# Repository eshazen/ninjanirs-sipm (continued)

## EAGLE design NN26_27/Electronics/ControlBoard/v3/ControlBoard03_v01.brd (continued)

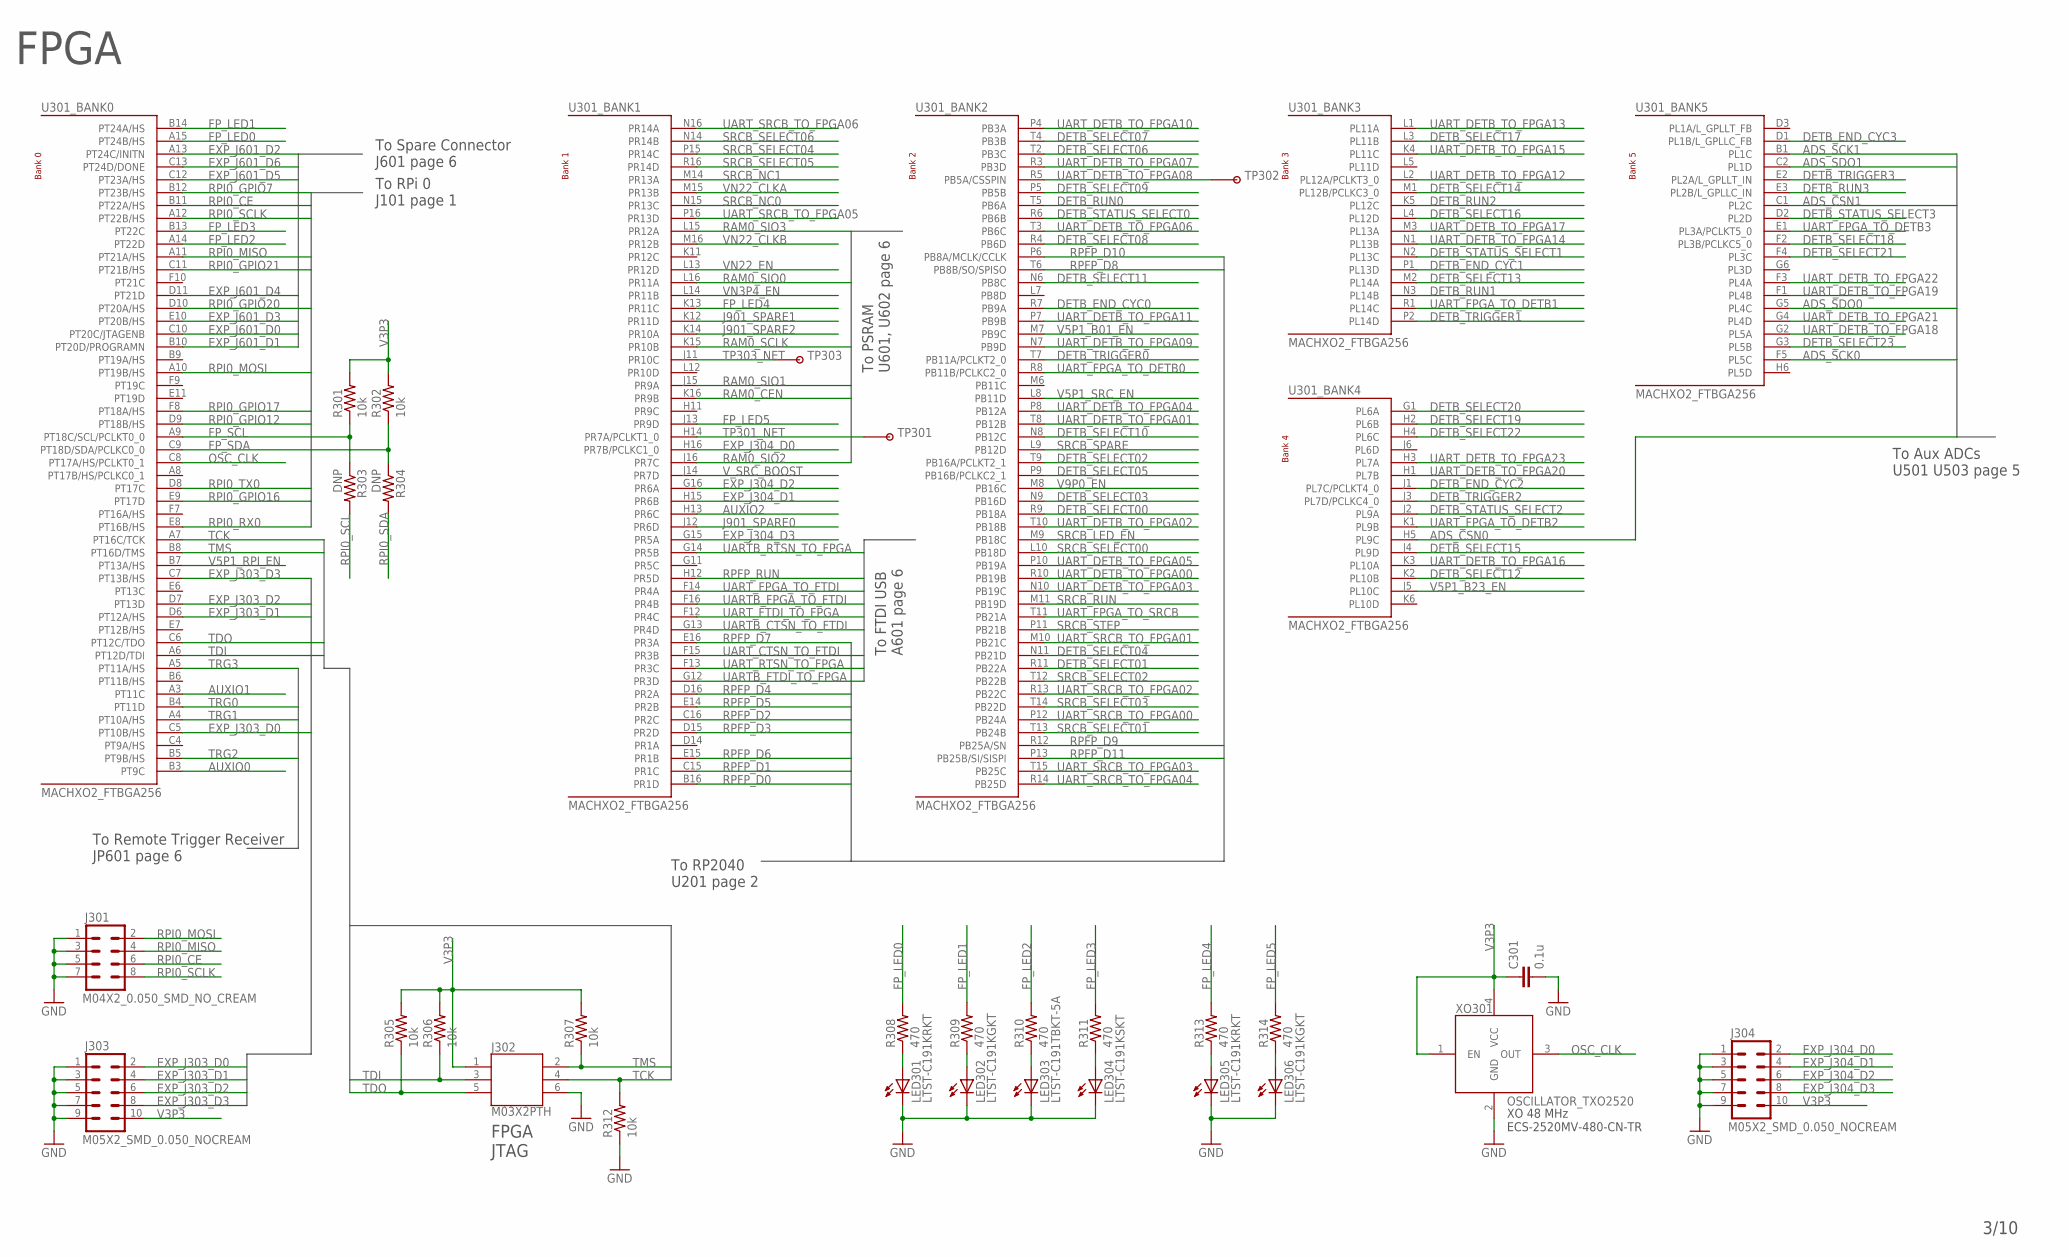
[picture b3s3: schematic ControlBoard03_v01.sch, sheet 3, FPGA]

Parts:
C301: 0.1u; 0402-CAP
J301: M04X2_0.050_SMD_NO_CREAM
J302: M03X2PTH; 2X3-NS
J303, J304: M05X2_SMD_0.050_NOCREAM; M05X2_0.050_SMD_NO_CREAM
LED301, LED305: LTST-C191KRKT; LED-0603
LED302, LED306: LTST-C191KGKT; LED-0603
LED303: LTST-C191TBKT-5A; LED-0603
LED304: LTST-C191KSKT; LED-0603
R301, R302, R305, R306, R307, R312: 10k; 0402-RES
R303, R304: DNP; 0402-RES
R308, R309, R310, R311, R313, R314: 470; 0402-RES
TP301, TP303: TESTPOINT_ROUND; TESTPAD_ROUND
TP302: TESTPOINTPADSMALL; TESTPAD_SMALL
U301: MACHXO2_FTBGA256; LBGA-256
XO301: OSCILLATOR_TXO2520; TXO2520

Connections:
ADS_CSN0: U301.H5 (PL9C); also elsewhere on the board
ADS_CSN1: U301.C1 (PL2C); also elsewhere on the board
ADS_SCK0: U301.F5 (PL5C); also elsewhere on the board
ADS_SCK1: U301.B1 (PL1C); also elsewhere on the board
ADS_SDO0: U301.G5 (PL4C); also elsewhere on the board
ADS_SDO1: U301.C2 (PL1D); also elsewhere on the board
AUXIO0: U301.B3 (PT9C); also elsewhere on the board
AUXIO1: U301.A3 (PT11C); also elsewhere on the board
AUXIO2: U301.H13 (PR6C); also elsewhere on the board
DETB_END_CYC0: U301.R7 (PB9A); also elsewhere on the board
DETB_END_CYC1: U301.P1 (PL13D); also elsewhere on the board
DETB_END_CYC2: U301.J1 (PL7C/PCLKT4_0); also elsewhere on the board
DETB_END_CYC3: U301.D1 (PL1B/L_GPLLC_FB); also elsewhere on the board
DETB_RUN0: U301.T5 (PB6A); also elsewhere on the board
DETB_RUN1: U301.N3 (PL14B); also elsewhere on the board
DETB_RUN2: U301.K5 (PL12C); also elsewhere on the board
DETB_RUN3: U301.E3 (PL2B/L_GPLLC_IN); also elsewhere on the board
DETB_SELECT00: U301.R9 (PB18A); also elsewhere on the board
DETB_SELECT01: U301.R11 (PB22A); also elsewhere on the board
DETB_SELECT02: U301.T9 (PB16A/PCLKT2_1); also elsewhere on the board
DETB_SELECT03: U301.N9 (PB16D); also elsewhere on the board
DETB_SELECT04: U301.N11 (PB21D); also elsewhere on the board
DETB_SELECT05: U301.P9 (PB16B/PCLKC2_1); also elsewhere on the board
DETB_SELECT06: U301.T2 (PB3C); also elsewhere on the board
DETB_SELECT07: U301.T4 (PB3B); also elsewhere on the board
DETB_SELECT08: U301.R4 (PB6D); also elsewhere on the board
DETB_SELECT09: U301.P5 (PB5B); also elsewhere on the board
DETB_SELECT10: U301.N8 (PB12C); also elsewhere on the board
DETB_SELECT11: U301.N6 (PB8C); also elsewhere on the board
DETB_SELECT12: U301.K2 (PL10B); also elsewhere on the board
DETB_SELECT13: U301.M2 (PL14A); also elsewhere on the board
DETB_SELECT14: U301.M1 (PL12B/PCLKC3_0); also elsewhere on the board
DETB_SELECT15: U301.J4 (PL9D); also elsewhere on the board
DETB_SELECT16: U301.L4 (PL12D); also elsewhere on the board
DETB_SELECT17: U301.L3 (PL11B); also elsewhere on the board
DETB_SELECT18: U301.F2 (PL3B/PCLKC5_0); also elsewhere on the board
DETB_SELECT19: U301.H2 (PL6B); also elsewhere on the board
DETB_SELECT20: U301.G1 (PL6A); also elsewhere on the board
DETB_SELECT21: U301.F4 (PL3C); also elsewhere on the board
DETB_SELECT22: U301.H4 (PL6C); also elsewhere on the board
DETB_SELECT23: U301.G3 (PL5B); also elsewhere on the board
DETB_STATUS_SELECT0: U301.R6 (PB6B); also elsewhere on the board
DETB_STATUS_SELECT1: U301.N2 (PL13C); also elsewhere on the board
DETB_STATUS_SELECT2: U301.J2 (PL9A); also elsewhere on the board
DETB_STATUS_SELECT3: U301.D2 (PL2D); also elsewhere on the board
DETB_TRIGGER0: U301.T7 (PB11A/PCLKT2_0); also elsewhere on the board
DETB_TRIGGER1: U301.P2 (PL14D); also elsewhere on the board
DETB_TRIGGER2: U301.J3 (PL7D/PCLKC4_0); also elsewhere on the board
DETB_TRIGGER3: U301.E2 (PL2A/L_GPLLT_IN); also elsewhere on the board
EXP_J303_D0: J303.2, U301.C5 (PT10B/HS)
EXP_J303_D1: J303.4, U301.D6 (PT12A/HS)
EXP_J303_D2: J303.6, U301.D7 (PT13D)
EXP_J303_D3: J303.8, U301.C7 (PT13B/HS)
EXP_J304_D0: J304.2, U301.H16 (PR7B/PCLKC1_0)
EXP_J304_D1: J304.4, U301.H15 (PR6B)
EXP_J304_D2: J304.6, U301.G16 (PR6A)
EXP_J304_D3: J304.8, U301.G15 (PR5A)
EXP_J601_D0: U301.C10 (PT20C/JTAGENB); also elsewhere on the board
EXP_J601_D1: U301.B10 (PT20D/PROGRAMN); also elsewhere on the board
EXP_J601_D2: U301.A13 (PT24C/INITN); also elsewhere on the board
EXP_J601_D3: U301.E10 (PT20B/HS); also elsewhere on the board
EXP_J601_D4: U301.D11 (PT21D); also elsewhere on the board
EXP_J601_D5: U301.C12 (PT23A/HS); also elsewhere on the board
EXP_J601_D6: U301.C13 (PT24D/DONE); also elsewhere on the board
FP_LED0: R308.2, U301.A15 (PT24B/HS)
FP_LED1: R309.2, U301.B14 (PT24A/HS)
FP_LED2: R310.2, U301.A14 (PT22D)
FP_LED3: R311.2, U301.B13 (PT22C)
FP_LED4: R313.2, U301.K13 (PR11C)
FP_LED5: R314.2, U301.J13 (PR9D)
FP_SCL: R301.1, R303.1, U301.A9 (PT18C/SCL/PCLKT0_0)
FP_SDA: R302.1, R304.1, U301.C9 (PT18D/SDA/PCLKC0_0)
GND: C301.2, J301.1, J301.3, J301.5, J301.7, J302.6, J303.1, J303.3, J303.5, J303.7, J303.9, J304.1, J304.3, J304.5, J304.7, J304.9, LED301.C, LED302.C, LED303.C, LED304.C, LED305.C, LED306.C, R312.1, XO301.2 (GND); also elsewhere on the board
J901_SPARE0: U301.J12 (PR6D); also elsewhere on the board
J901_SPARE1: U301.K12 (PR11D); also elsewhere on the board
J901_SPARE2: U301.K14 (PR10A); also elsewhere on the board
unnamed: LED301.A, R308.1
unnamed: LED302.A, R309.1
unnamed: LED303.A, R310.1
unnamed: LED304.A, R311.1
unnamed: LED305.A, R313.1
unnamed: LED306.A, R314.1
OSC_CLK: U301.C8 (PT17A/HS/PCLKT0_1), XO301.3 (OUT)
RAM0_CEN: U301.K16 (PR9B); also elsewhere on the board
RAM0_SCLK: U301.K15 (PR10B); also elsewhere on the board
RAM0_SIO0: U301.L16 (PR11A); also elsewhere on the board
RAM0_SIO1: U301.J15 (PR9A); also elsewhere on the board
RAM0_SIO2: U301.J16 (PR7C); also elsewhere on the board
RAM0_SIO3: U301.L15 (PR12A); also elsewhere on the board
RPFP_D0: U301.B16 (PR1D); also elsewhere on the board
RPFP_D1: U301.C15 (PR1C); also elsewhere on the board
RPFP_D2: U301.C16 (PR2C); also elsewhere on the board
RPFP_D3: U301.D15 (PR2D); also elsewhere on the board
RPFP_D4: U301.D16 (PR2A); also elsewhere on the board
RPFP_D5: U301.E14 (PR2B); also elsewhere on the board
RPFP_D6: U301.E15 (PR1B); also elsewhere on the board
RPFP_D7: U301.E16 (PR3A); also elsewhere on the board
RPFP_D8: U301.T6 (PB8B/SO/SPISO); also elsewhere on the board
RPFP_D9: U301.R12 (PB25A/SN); also elsewhere on the board
RPFP_D10: U301.P6 (PB8A/MCLK/CCLK); also elsewhere on the board
RPFP_D11: U301.P13 (PB25B/SI/SISPI); also elsewhere on the board
RPFP_RUN: U301.H12 (PR5D); also elsewhere on the board
RPI0_CE: J301.6, U301.B11 (PT22A/HS); also elsewhere on the board
RPI0_GPIO7: U301.B12 (PT23B/HS); also elsewhere on the board
RPI0_GPIO12: U301.D9 (PT18B/HS); also elsewhere on the board
RPI0_GPIO16: U301.E9 (PT17D); also elsewhere on the board
RPI0_GPIO17: U301.F8 (PT18A/HS); also elsewhere on the board
RPI0_GPIO20: U301.D10 (PT20A/HS); also elsewhere on the board
RPI0_GPIO21: U301.C11 (PT21B/HS); also elsewhere on the board
RPI0_MISO: J301.4, U301.A11 (PT21A/HS); also elsewhere on the board
RPI0_MOSI: J301.2, U301.A10 (PT19B/HS); also elsewhere on the board
RPI0_RX0: U301.E8 (PT16B/HS); also elsewhere on the board
RPI0_SCL: R303.2; also elsewhere on the board
RPI0_SCLK: J301.8, U301.A12 (PT22B/HS); also elsewhere on the board
RPI0_SDA: R304.2; also elsewhere on the board
RPI0_TX0: U301.D8 (PT17C); also elsewhere on the board
SRCB_LED_EN: U301.M9 (PB18C); also elsewhere on the board
SRCB_NC0: U301.N15 (PR13C); also elsewhere on the board
SRCB_NC1: U301.M14 (PR13A); also elsewhere on the board
SRCB_RUN: U301.M11 (PB19D); also elsewhere on the board
SRCB_SELECT00: U301.L10 (PB18D); also elsewhere on the board
SRCB_SELECT01: U301.T13 (PB24B); also elsewhere on the board
SRCB_SELECT02: U301.T12 (PB22B); also elsewhere on the board
SRCB_SELECT03: U301.T14 (PB22D); also elsewhere on the board
SRCB_SELECT04: U301.P15 (PR14C); also elsewhere on the board
SRCB_SELECT05: U301.R16 (PR14D); also elsewhere on the board
SRCB_SELECT06: U301.N14 (PR14B); also elsewhere on the board
SRCB_SPARE: U301.L9 (PB12D); also elsewhere on the board
SRCB_STEP: U301.P11 (PB21B); also elsewhere on the board
TCK: J302.4, R312.2, U301.A7 (PT16C/TCK)
TDI: J302.3, R306.1, U301.A6 (PT12D/TDI)
TDO: J302.5, R305.1, U301.C6 (PT12C/TDO)
TMS: J302.2, R307.1, U301.B8 (PT16D/TMS)
TP301_NET: TP301.P$1, U301.H14 (PR7A/PCLKT1_0)
TP303_NET: TP303.P$1, U301.J11 (PR10C)
TRG0: U301.B4 (PT11D); also elsewhere on the board
TRG1: U301.A4 (PT10A/HS); also elsewhere on the board
TRG2: U301.B5 (PT9B/HS); also elsewhere on the board
TRG3: U301.A5 (PT11A/HS); also elsewhere on the board
UARTB_CTSN_TO_FTDI: U301.G13 (PR4D); also elsewhere on the board
UARTB_FPGA_TO_FTDI: U301.F16 (PR4B); also elsewhere on the board
UARTB_FTDI_TO_FPGA: U301.G12 (PR3D); also elsewhere on the board
UARTB_RTSN_TO_FPGA: U301.G14 (PR5B); also elsewhere on the board
UART_CTSN_TO_FTDI: U301.F15 (PR3B); also elsewhere on the board
UART_DETB_TO_FPGA00: U301.R10 (PB19B); also elsewhere on the board
UART_DETB_TO_FPGA01: U301.T8 (PB12B); also elsewhere on the board
UART_DETB_TO_FPGA02: U301.T10 (PB18B); also elsewhere on the board
UART_DETB_TO_FPGA03: U301.N10 (PB19C); also elsewhere on the board
UART_DETB_TO_FPGA04: U301.P8 (PB12A); also elsewhere on the board
UART_DETB_TO_FPGA05: U301.P10 (PB19A); also elsewhere on the board
UART_DETB_TO_FPGA06: U301.T3 (PB6C); also elsewhere on the board
UART_DETB_TO_FPGA07: U301.R3 (PB3D); also elsewhere on the board
UART_DETB_TO_FPGA08: TP302.P$1, U301.R5 (PB5A/CSSPIN); also elsewhere on the board
UART_DETB_TO_FPGA09: U301.N7 (PB9D); also elsewhere on the board
UART_DETB_TO_FPGA10: U301.P4 (PB3A); also elsewhere on the board
UART_DETB_TO_FPGA11: U301.P7 (PB9B); also elsewhere on the board
UART_DETB_TO_FPGA12: U301.L2 (PL12A/PCLKT3_0); also elsewhere on the board
UART_DETB_TO_FPGA13: U301.L1 (PL11A); also elsewhere on the board
UART_DETB_TO_FPGA14: U301.N1 (PL13B); also elsewhere on the board
UART_DETB_TO_FPGA15: U301.K4 (PL11C); also elsewhere on the board
UART_DETB_TO_FPGA16: U301.K3 (PL10A); also elsewhere on the board
UART_DETB_TO_FPGA17: U301.M3 (PL13A); also elsewhere on the board
UART_DETB_TO_FPGA18: U301.G2 (PL5A); also elsewhere on the board
UART_DETB_TO_FPGA19: U301.F1 (PL4B); also elsewhere on the board
UART_DETB_TO_FPGA20: U301.H1 (PL7B); also elsewhere on the board
UART_DETB_TO_FPGA21: U301.G4 (PL4D); also elsewhere on the board
UART_DETB_TO_FPGA22: U301.F3 (PL4A); also elsewhere on the board
UART_DETB_TO_FPGA23: U301.H3 (PL7A); also elsewhere on the board
UART_FPGA_TO_DETB0: U301.R8 (PB11B/PCLKC2_0); also elsewhere on the board
UART_FPGA_TO_DETB1: U301.R1 (PL14C); also elsewhere on the board
UART_FPGA_TO_DETB2: U301.K1 (PL9B); also elsewhere on the board
UART_FPGA_TO_DETB3: U301.E1 (PL3A/PCLKT5_0); also elsewhere on the board
UART_FPGA_TO_FTDI: U301.F14 (PR4A); also elsewhere on the board
UART_FPGA_TO_SRCB: U301.T11 (PB21A); also elsewhere on the board
UART_FTDI_TO_FPGA: U301.F12 (PR4C); also elsewhere on the board
UART_RTSN_TO_FPGA: U301.F13 (PR3C); also elsewhere on the board
UART_SRCB_TO_FPGA00: U301.P12 (PB24A); also elsewhere on the board
UART_SRCB_TO_FPGA01: U301.M10 (PB21C); also elsewhere on the board
UART_SRCB_TO_FPGA02: U301.R13 (PB22C); also elsewhere on the board
UART_SRCB_TO_FPGA03: U301.T15 (PB25C); also elsewhere on the board
UART_SRCB_TO_FPGA04: U301.R14 (PB25D); also elsewhere on the board
UART_SRCB_TO_FPGA05: U301.P16 (PR13D); also elsewhere on the board
UART_SRCB_TO_FPGA06: U301.N16 (PR14A); also elsewhere on the board
V3P3: C301.1, J302.1, J303.10, J304.10, R301.2, R302.2, R305.2, R306.2, R307.2, XO301.1 (EN), XO301.4 (VCC); also elsewhere on the board
V5P1_B01_EN: U301.M7 (PB9C); also elsewhere on the board
V5P1_B23_EN: U301.J5 (PL10C); also elsewhere on the board
V5P1_RPI_EN: U301.B7 (PT13A/HS); also elsewhere on the board
V5P1_SRC_EN: U301.L8 (PB11D); also elsewhere on the board
V9P0_EN: U301.M8 (PB16C); also elsewhere on the board
VN3P4_EN: U301.L14 (PR11B); also elsewhere on the board
VN22_CLKA: U301.M15 (PR13B); also elsewhere on the board
VN22_CLKB: U301.M16 (PR12B); also elsewhere on the board
VN22_EN: U301.L13 (PR12D); also elsewhere on the board
V_SRC_BOOST: U301.J14 (PR7D); also elsewhere on the board

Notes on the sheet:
XO 48 MHz ECS-2520MV-480-CN-TR
FPGA
FPGA JTAG
To RPi 0 J101 page 1
To RP2040 U201 page 2
To FTDI USB A601 page 6
To Spare Connector J601 page 6
To Remote Trigger Receiver JP601 page 6
To Aux ADCs U501 U503 page 5
To PSRAM U601, U602 page 6

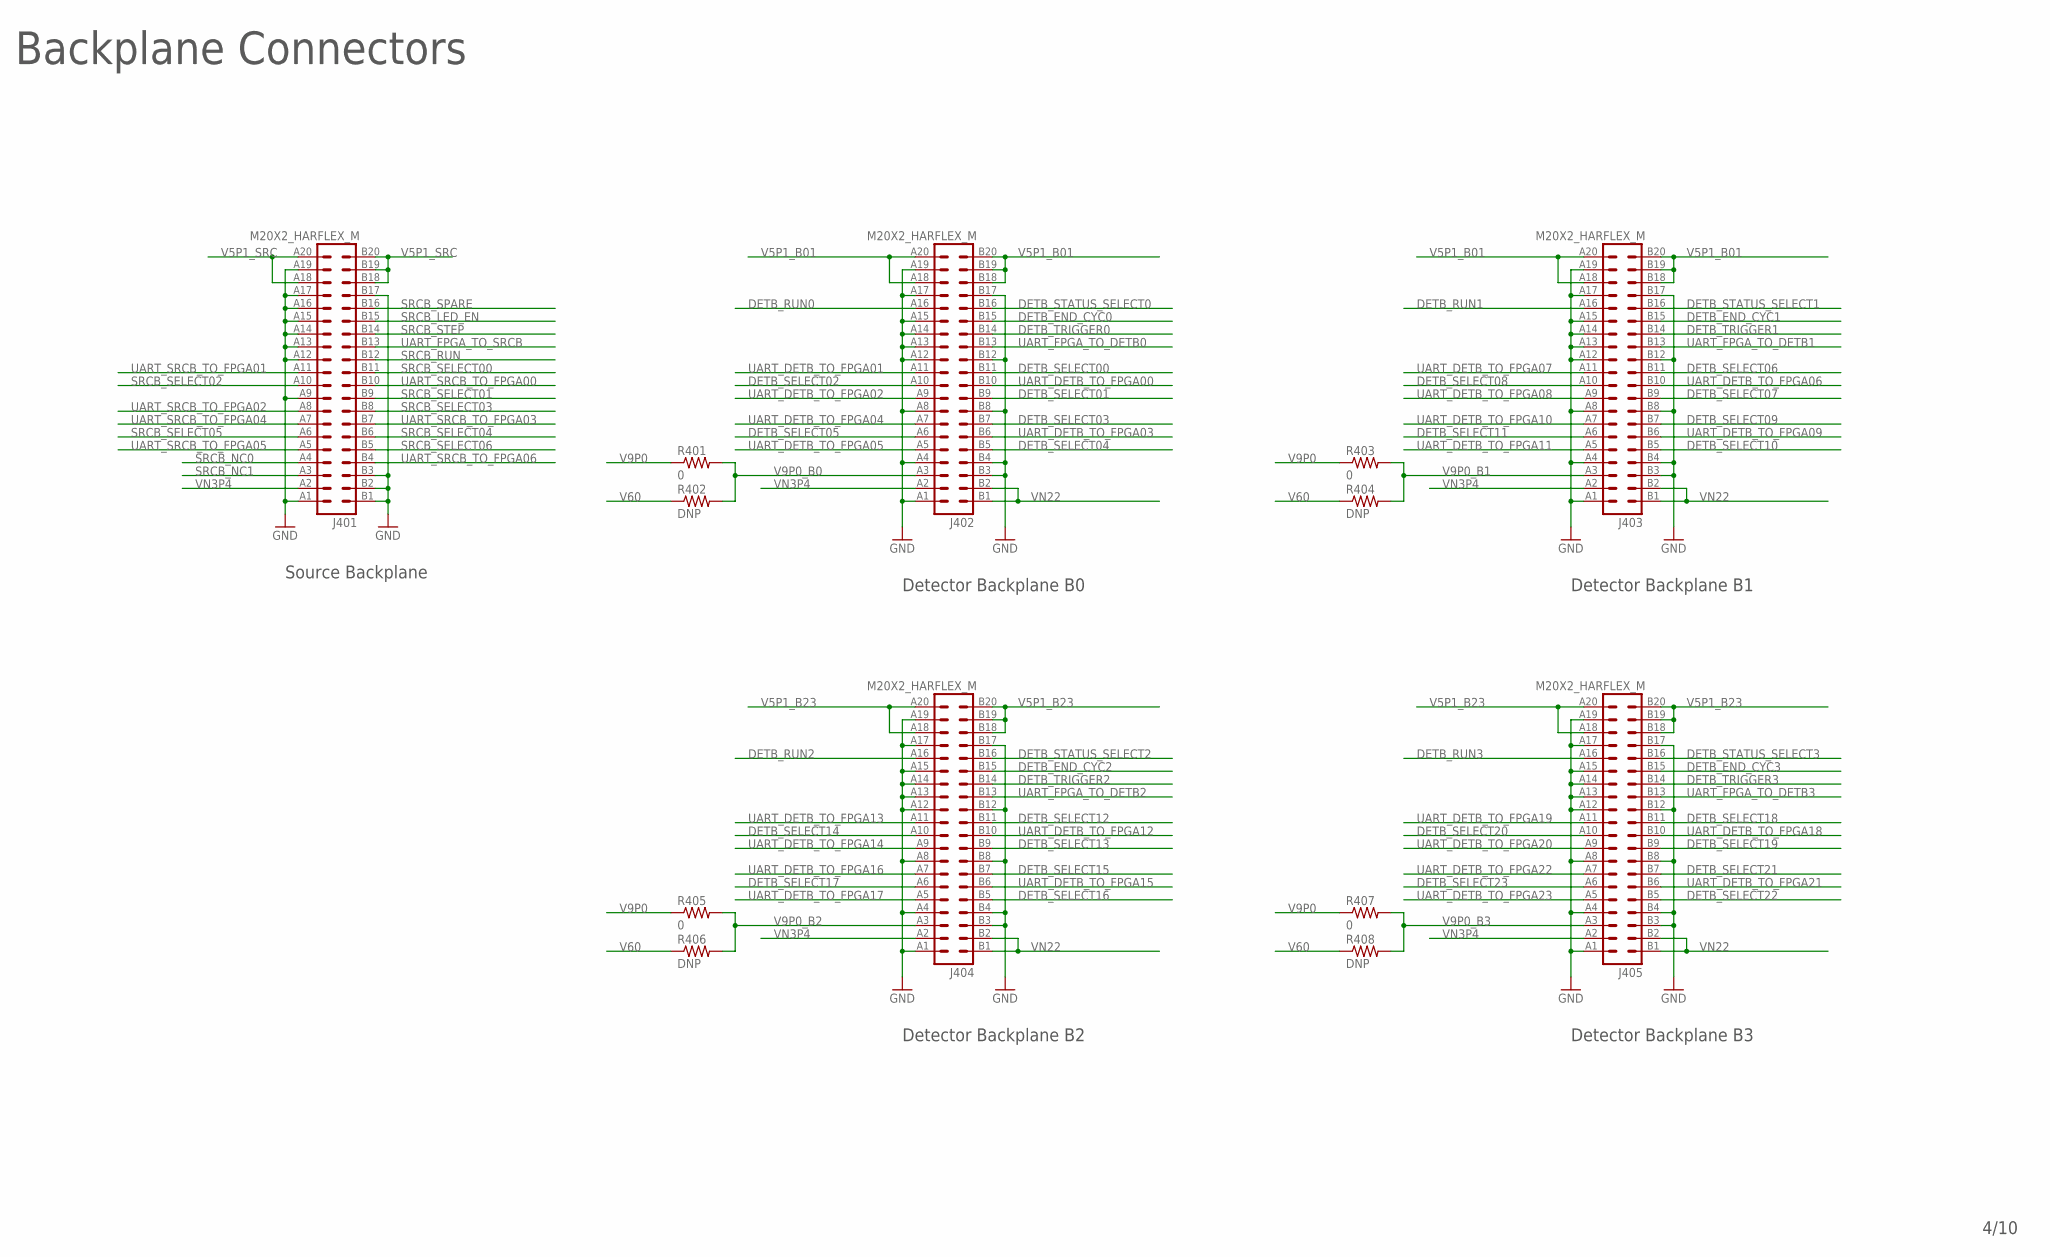
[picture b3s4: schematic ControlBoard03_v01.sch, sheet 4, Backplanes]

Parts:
J401, J402, J403, J404, J405: M20X2_HARFLEX_M
R401, R403, R405, R407: 0; 0603-RES
R402, R404, R406, R408: DNP; 0603-RES

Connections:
DETB_END_CYC0: J402.B15 (29); also elsewhere on the board
DETB_END_CYC1: J403.B15 (29); also elsewhere on the board
DETB_END_CYC2: J404.B15 (29); also elsewhere on the board
DETB_END_CYC3: J405.B15 (29); also elsewhere on the board
DETB_RUN0: J402.A16 (32); also elsewhere on the board
DETB_RUN1: J403.A16 (32); also elsewhere on the board
DETB_RUN2: J404.A16 (32); also elsewhere on the board
DETB_RUN3: J405.A16 (32); also elsewhere on the board
DETB_SELECT00: J402.B11 (21); also elsewhere on the board
DETB_SELECT01: J402.B9 (17); also elsewhere on the board
DETB_SELECT02: J402.A10 (20); also elsewhere on the board
DETB_SELECT03: J402.B7 (13); also elsewhere on the board
DETB_SELECT04: J402.B5 (9); also elsewhere on the board
DETB_SELECT05: J402.A6 (12); also elsewhere on the board
DETB_SELECT06: J403.B11 (21); also elsewhere on the board
DETB_SELECT07: J403.B9 (17); also elsewhere on the board
DETB_SELECT08: J403.A10 (20); also elsewhere on the board
DETB_SELECT09: J403.B7 (13); also elsewhere on the board
DETB_SELECT10: J403.B5 (9); also elsewhere on the board
DETB_SELECT11: J403.A6 (12); also elsewhere on the board
DETB_SELECT12: J404.B11 (21); also elsewhere on the board
DETB_SELECT13: J404.B9 (17); also elsewhere on the board
DETB_SELECT14: J404.A10 (20); also elsewhere on the board
DETB_SELECT15: J404.B7 (13); also elsewhere on the board
DETB_SELECT16: J404.B5 (9); also elsewhere on the board
DETB_SELECT17: J404.A6 (12); also elsewhere on the board
DETB_SELECT18: J405.B11 (21); also elsewhere on the board
DETB_SELECT19: J405.B9 (17); also elsewhere on the board
DETB_SELECT20: J405.A10 (20); also elsewhere on the board
DETB_SELECT21: J405.B7 (13); also elsewhere on the board
DETB_SELECT22: J405.B5 (9); also elsewhere on the board
DETB_SELECT23: J405.A6 (12); also elsewhere on the board
DETB_STATUS_SELECT0: J402.B16 (31); also elsewhere on the board
DETB_STATUS_SELECT1: J403.B16 (31); also elsewhere on the board
DETB_STATUS_SELECT2: J404.B16 (31); also elsewhere on the board
DETB_STATUS_SELECT3: J405.B16 (31); also elsewhere on the board
DETB_TRIGGER0: J402.B14 (27); also elsewhere on the board
DETB_TRIGGER1: J403.B14 (27); also elsewhere on the board
DETB_TRIGGER2: J404.B14 (27); also elsewhere on the board
DETB_TRIGGER3: J405.B14 (27); also elsewhere on the board
GND: J401.A1 (2), J401.A9 (18), J401.A12 (24), J401.A13 (26), J401.A14 (28), J401.A15 (30), J401.A16 (32), J401.A17 (34), J401.A19 (38), J401.B1 (1), J401.B2 (3), J401.B3 (5), J401.B17 (33), J402.A1 (2), J402.A4 (8), J402.A8 (16), J402.A12 (24), J402.A13 (26), J402.A14 (28), J402.A15 (30), J402.A17 (34), J402.A19 (38), J402.B3 (5), J402.B4 (7), J402.B8 (15), J402.B12 (23), J402.B17 (33), J403.A1 (2), J403.A4 (8), J403.A8 (16), J403.A12 (24), J403.A13 (26), J403.A14 (28), J403.A15 (30), J403.A17 (34), J403.A19 (38), J403.B3 (5), J403.B4 (7), J403.B8 (15), J403.B12 (23), J403.B17 (33), J404.A1 (2), J404.A4 (8), J404.A8 (16), J404.A12 (24), J404.A13 (26), J404.A14 (28), J404.A15 (30), J404.A17 (34), J404.A19 (38), J404.B3 (5), J404.B4 (7), J404.B8 (15), J404.B12 (23), J404.B17 (33), J405.A1 (2), J405.A4 (8), J405.A8 (16), J405.A12 (24), J405.A13 (26), J405.A14 (28), J405.A15 (30), J405.A17 (34), J405.A19 (38), J405.B3 (5), J405.B4 (7), J405.B8 (15), J405.B12 (23), J405.B17 (33); also elsewhere on the board
SRCB_LED_EN: J401.B15 (29); also elsewhere on the board
SRCB_NC0: J401.A4 (8); also elsewhere on the board
SRCB_NC1: J401.A3 (6); also elsewhere on the board
SRCB_RUN: J401.B12 (23); also elsewhere on the board
SRCB_SELECT00: J401.B11 (21); also elsewhere on the board
SRCB_SELECT01: J401.B9 (17); also elsewhere on the board
SRCB_SELECT02: J401.A10 (20); also elsewhere on the board
SRCB_SELECT03: J401.B8 (15); also elsewhere on the board
SRCB_SELECT04: J401.B6 (11); also elsewhere on the board
SRCB_SELECT05: J401.A6 (12); also elsewhere on the board
SRCB_SELECT06: J401.B5 (9); also elsewhere on the board
SRCB_SPARE: J401.B16 (31); also elsewhere on the board
SRCB_STEP: J401.B14 (27); also elsewhere on the board
UART_DETB_TO_FPGA00: J402.B10 (19); also elsewhere on the board
UART_DETB_TO_FPGA01: J402.A11 (22); also elsewhere on the board
UART_DETB_TO_FPGA02: J402.A9 (18); also elsewhere on the board
UART_DETB_TO_FPGA03: J402.B6 (11); also elsewhere on the board
UART_DETB_TO_FPGA04: J402.A7 (14); also elsewhere on the board
UART_DETB_TO_FPGA05: J402.A5 (10); also elsewhere on the board
UART_DETB_TO_FPGA06: J403.B10 (19); also elsewhere on the board
UART_DETB_TO_FPGA07: J403.A11 (22); also elsewhere on the board
UART_DETB_TO_FPGA08: J403.A9 (18); also elsewhere on the board
UART_DETB_TO_FPGA09: J403.B6 (11); also elsewhere on the board
UART_DETB_TO_FPGA10: J403.A7 (14); also elsewhere on the board
UART_DETB_TO_FPGA11: J403.A5 (10); also elsewhere on the board
UART_DETB_TO_FPGA12: J404.B10 (19); also elsewhere on the board
UART_DETB_TO_FPGA13: J404.A11 (22); also elsewhere on the board
UART_DETB_TO_FPGA14: J404.A9 (18); also elsewhere on the board
UART_DETB_TO_FPGA15: J404.B6 (11); also elsewhere on the board
UART_DETB_TO_FPGA16: J404.A7 (14); also elsewhere on the board
UART_DETB_TO_FPGA17: J404.A5 (10); also elsewhere on the board
UART_DETB_TO_FPGA18: J405.B10 (19); also elsewhere on the board
UART_DETB_TO_FPGA19: J405.A11 (22); also elsewhere on the board
UART_DETB_TO_FPGA20: J405.A9 (18); also elsewhere on the board
UART_DETB_TO_FPGA21: J405.B6 (11); also elsewhere on the board
UART_DETB_TO_FPGA22: J405.A7 (14); also elsewhere on the board
UART_DETB_TO_FPGA23: J405.A5 (10); also elsewhere on the board
UART_FPGA_TO_DETB0: J402.B13 (25); also elsewhere on the board
UART_FPGA_TO_DETB1: J403.B13 (25); also elsewhere on the board
UART_FPGA_TO_DETB2: J404.B13 (25); also elsewhere on the board
UART_FPGA_TO_DETB3: J405.B13 (25); also elsewhere on the board
UART_FPGA_TO_SRCB: J401.B13 (25); also elsewhere on the board
UART_SRCB_TO_FPGA00: J401.B10 (19); also elsewhere on the board
UART_SRCB_TO_FPGA01: J401.A11 (22); also elsewhere on the board
UART_SRCB_TO_FPGA02: J401.A8 (16); also elsewhere on the board
UART_SRCB_TO_FPGA03: J401.B7 (13); also elsewhere on the board
UART_SRCB_TO_FPGA04: J401.A7 (14); also elsewhere on the board
UART_SRCB_TO_FPGA05: J401.A5 (10); also elsewhere on the board
UART_SRCB_TO_FPGA06: J401.B4 (7); also elsewhere on the board
V5P1_B01: J402.A18 (36), J402.A20 (40), J402.B18 (35), J402.B19 (37), J402.B20 (39), J403.A18 (36), J403.A20 (40), J403.B18 (35), J403.B19 (37), J403.B20 (39); also elsewhere on the board
V5P1_B23: J404.A18 (36), J404.A20 (40), J404.B18 (35), J404.B19 (37), J404.B20 (39), J405.A18 (36), J405.A20 (40), J405.B18 (35), J405.B19 (37), J405.B20 (39); also elsewhere on the board
V5P1_SRC: J401.A18 (36), J401.A20 (40), J401.B18 (35), J401.B19 (37), J401.B20 (39); also elsewhere on the board
V9P0: R401.1, R403.1, R405.1, R407.1; also elsewhere on the board
V9P0_B0: J402.A3 (6), R401.2, R402.2
V9P0_B1: J403.A3 (6), R403.2, R404.2
V9P0_B2: J404.A3 (6), R405.2, R406.2
V9P0_B3: J405.A3 (6), R407.2, R408.2
V60: R402.1, R404.1, R406.1, R408.1; also elsewhere on the board
VN3P4: J401.A2 (4), J402.A2 (4), J403.A2 (4), J404.A2 (4), J405.A2 (4); also elsewhere on the board
VN22: J402.B1 (1), J402.B2 (3), J403.B1 (1), J403.B2 (3), J404.B1 (1), J404.B2 (3), J405.B1 (1), J405.B2 (3); also elsewhere on the board

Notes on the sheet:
Backplane Connectors
Source Backplane
Detector Backplane B0
Detector Backplane B1
Detector Backplane B2
Detector Backplane B3

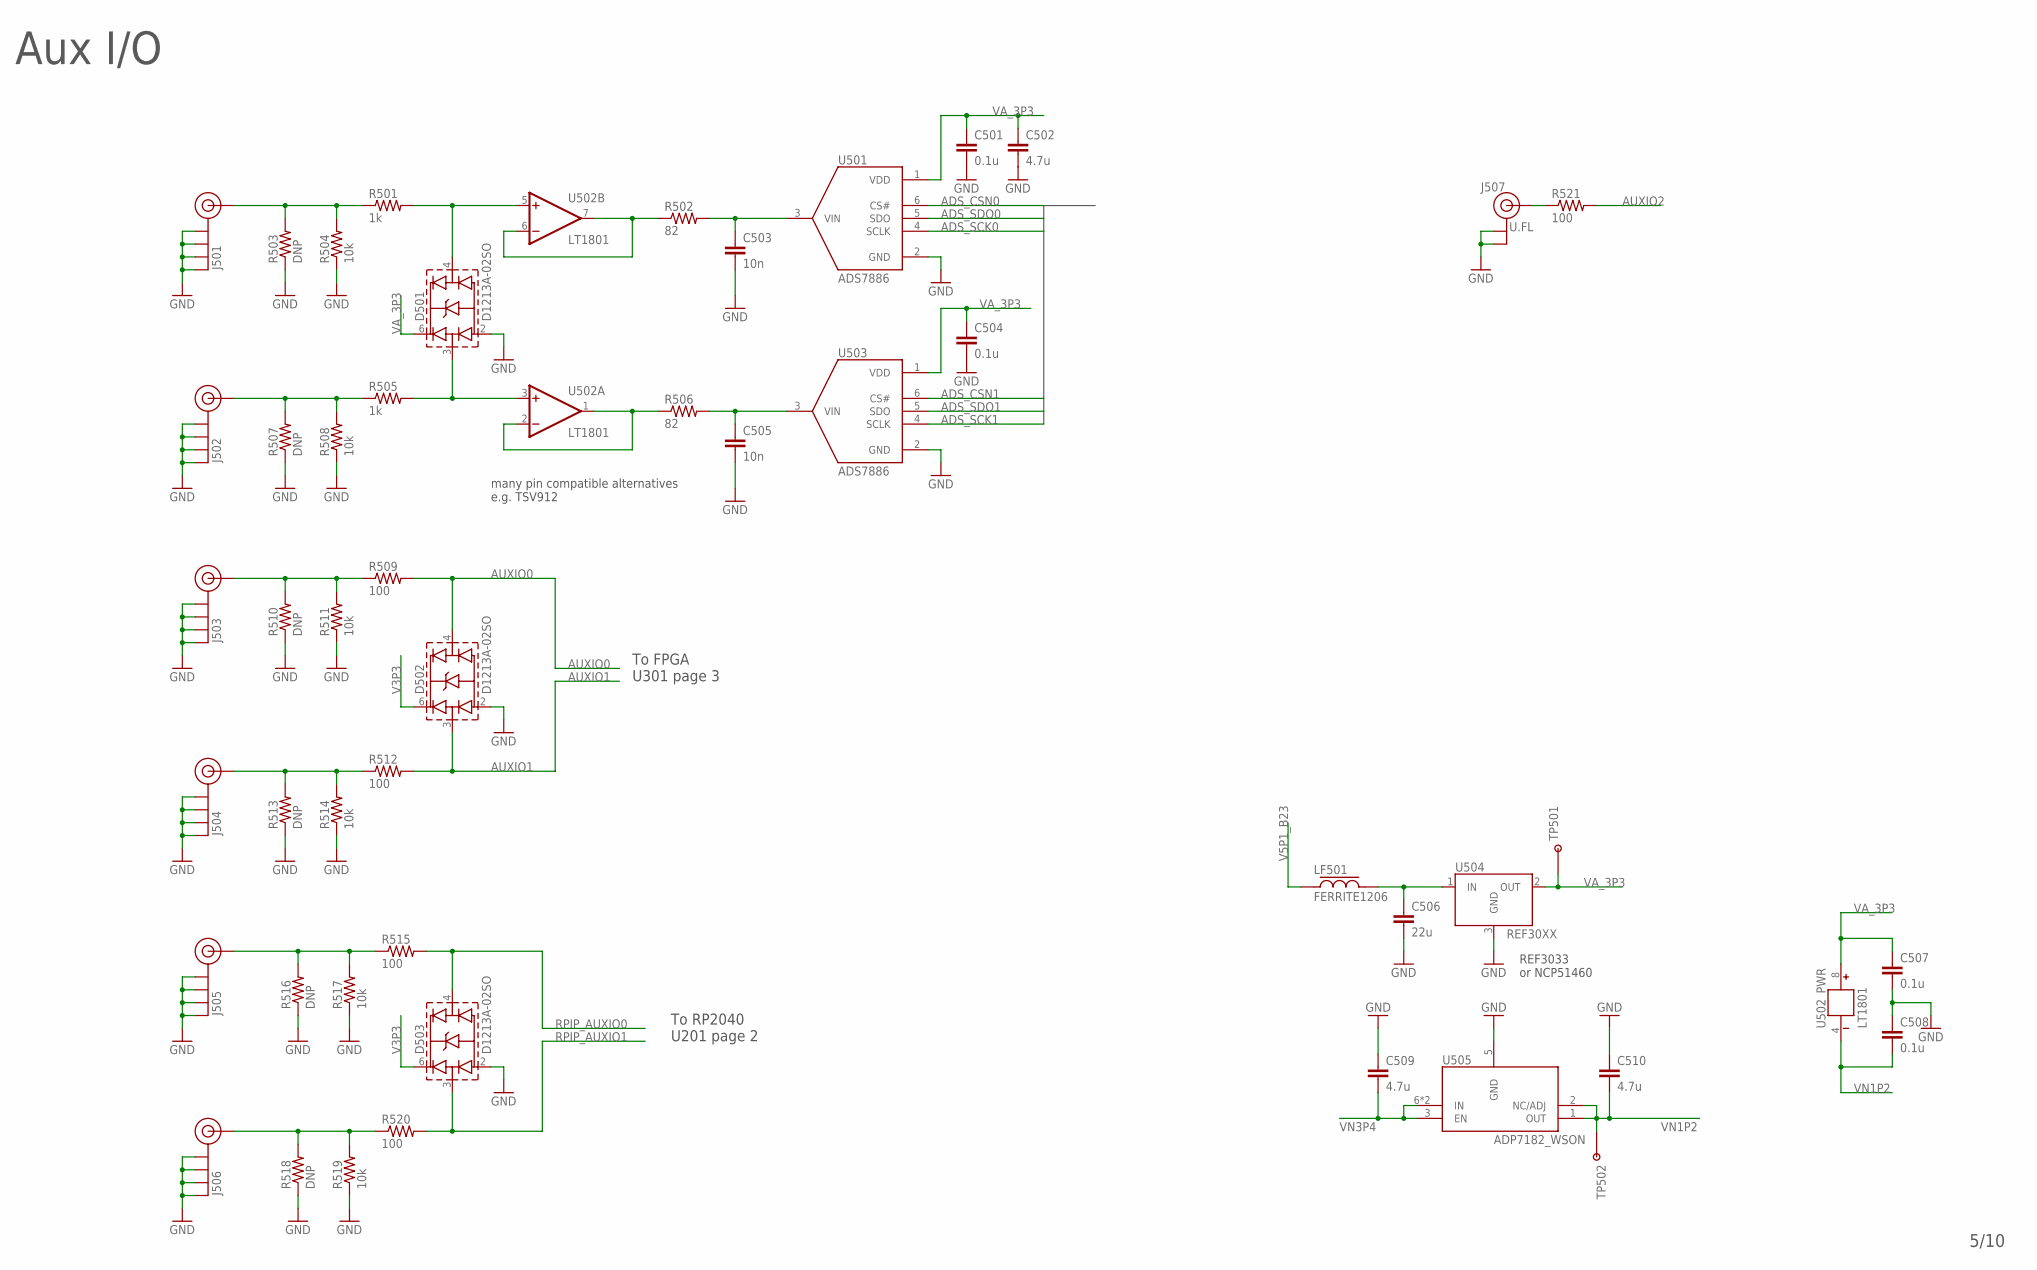
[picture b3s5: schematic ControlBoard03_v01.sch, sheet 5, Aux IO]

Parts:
C501, C504, C507, C508: 0.1u; 0402-CAP
C502, C509, C510: 4.7u; 0402-CAP
C503, C505: 10n; 0603-CAP
C506: 22u; 0805-CAP
D501, D502, D503: D1213A-02SO; SOT23-6
J501, J502, J503, J504, J505, J506: SMA_MMCX_PTH_RA; MMCX_PTH_RA
J507: U.FL
LF501: FERRITE1206; 1206
R501, R505: 1k; 0402-RES
R502, R506: 82; 0402-RES
R503, R507, R510, R513, R516, R518: DNP; 0805
R504, R508, R511, R514, R517, R519: 10k; 0402-RES
R509, R512, R515, R520, R521: 100; 0402-RES
TP501, TP502: TESTPOINT_ROUND; TESTPAD_ROUND
U501, U503: ADS7886; SOT363
U502: LT1801; SOP65P490X110-8N
U504: REF30XX; SOT23-3
U505: ADP7182_WSON; WSON6

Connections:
ADS_CSN0: U501.6 (CS#); also elsewhere on the board
ADS_CSN1: U503.6 (CS#); also elsewhere on the board
ADS_SCK0: U501.4 (SCLK); also elsewhere on the board
ADS_SCK1: U503.4 (SCLK); also elsewhere on the board
ADS_SDO0: U501.5 (SDO); also elsewhere on the board
ADS_SDO1: U503.5 (SDO); also elsewhere on the board
AUXIO0: D502.4 (CH2), R509.2; also elsewhere on the board
AUXIO1: D502.3 (CH1), R512.2; also elsewhere on the board
AUXIO2: R521.2; also elsewhere on the board
GND: C501.2, C502.2, C503.2, C504.2, C505.2, C506.2, C507.2, C508.1, C509.1, C510.1, D501.2 (VN), D502.2 (VN), D503.2 (VN), J501.G@1 (GND), J501.G@2 (GND), J501.G@3 (GND), J501.G@4 (GND), J502.G@1 (GND), J502.G@2 (GND), J502.G@3 (GND), J502.G@4 (GND), J503.G@1 (GND), J503.G@2 (GND), J503.G@3 (GND), J503.G@4 (GND), J504.G@1 (GND), J504.G@2 (GND), J504.G@3 (GND), J504.G@4 (GND), J505.G@1 (GND), J505.G@2 (GND), J505.G@3 (GND), J505.G@4 (GND), J506.G@1 (GND), J506.G@2 (GND), J506.G@3 (GND), J506.G@4 (GND), J507.P$1 (GND), J507.P$2 (GND), R503.1, R504.1, R507.1, R508.1, R510.1, R511.1, R513.1, R514.1, R516.1, R517.1, R518.1, R519.1, U501.2 (GND), U503.2 (GND), U504.3 (GND), U505.5 (GND); also elsewhere on the board
unnamed: J501.C (SIGNAL), R501.1, R503.2, R504.2
unnamed: D501.4 (CH2), R501.2, U502.5 (+IN)
unnamed: J502.C (SIGNAL), R505.1, R507.2, R508.2
unnamed: D501.3 (CH1), R505.2, U502.3 (+IN)
unnamed: J505.C (SIGNAL), R515.1, R516.2, R517.2
unnamed: J503.C (SIGNAL), R509.1, R510.2, R511.2
unnamed: J504.C (SIGNAL), R512.1, R513.2, R514.2
unnamed: C503.1, R502.2, U501.3 (VIN)
unnamed: R502.1, U502.6 (-IN), U502.7 (OUT)
unnamed: C505.1, R506.2, U503.3 (VIN)
unnamed: R506.1, U502.1 (OUT), U502.2 (-IN)
unnamed: J507.P$3 (SIGNAL), R521.1
unnamed: J506.C (SIGNAL), R518.2, R519.2, R520.1
unnamed: C506.1, LF501.2, U504.1 (IN)
RPIP_AUXIO0: D503.4 (CH2), R515.2; also elsewhere on the board
RPIP_AUXIO1: D503.3 (CH1), R520.2; also elsewhere on the board
V3P3: D502.6 (VP), D503.6 (VP); also elsewhere on the board
V5P1_B23: LF501.1; also elsewhere on the board
VA_3P3: C501.1, C502.1, C504.1, C507.1, D501.6 (VP), TP501.P$1, U501.1 (VDD), U502.8 (V+), U503.1 (VDD), U504.2 (OUT)
VN1P2: C508.2, C510.2, TP502.P$1, U502.4 (V-), U505.1 (OUT), U505.2 (NC/ADJ)
VN3P4: C509.2, U505.3 (EN), U505.6 (IN), U505.PAD (IN); also elsewhere on the board

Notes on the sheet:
many pin compatible alternatives e.g. TSV912
Aux I/O
REF3033 or NCP51460
To FPGA U301 page 3
To RP2040 U201 page 2
